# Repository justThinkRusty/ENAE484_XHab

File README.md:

# ENAE484_XHab
 This is a repository for Class of 2020 X-Hab Capstone Projecct revision and repository control. 
Unfortunately, due to the non-binary nature of NX files, collaboration between individuals in sub 
teams is going to be necessary to avoid merge conflicts (i.e. when two individuals work on the 
same assmebly file at the same time). If this occurs, one person's adjustments must be discarded
to be able to keep the repository moving. 

Additionally, please make comments with every commit to your branch so everyone can be up to date
with what changes were made. 

More subfolders can (and should) be made as we progress through the project, potentially such as
a Matlab folder or a Big Picture CAD program.

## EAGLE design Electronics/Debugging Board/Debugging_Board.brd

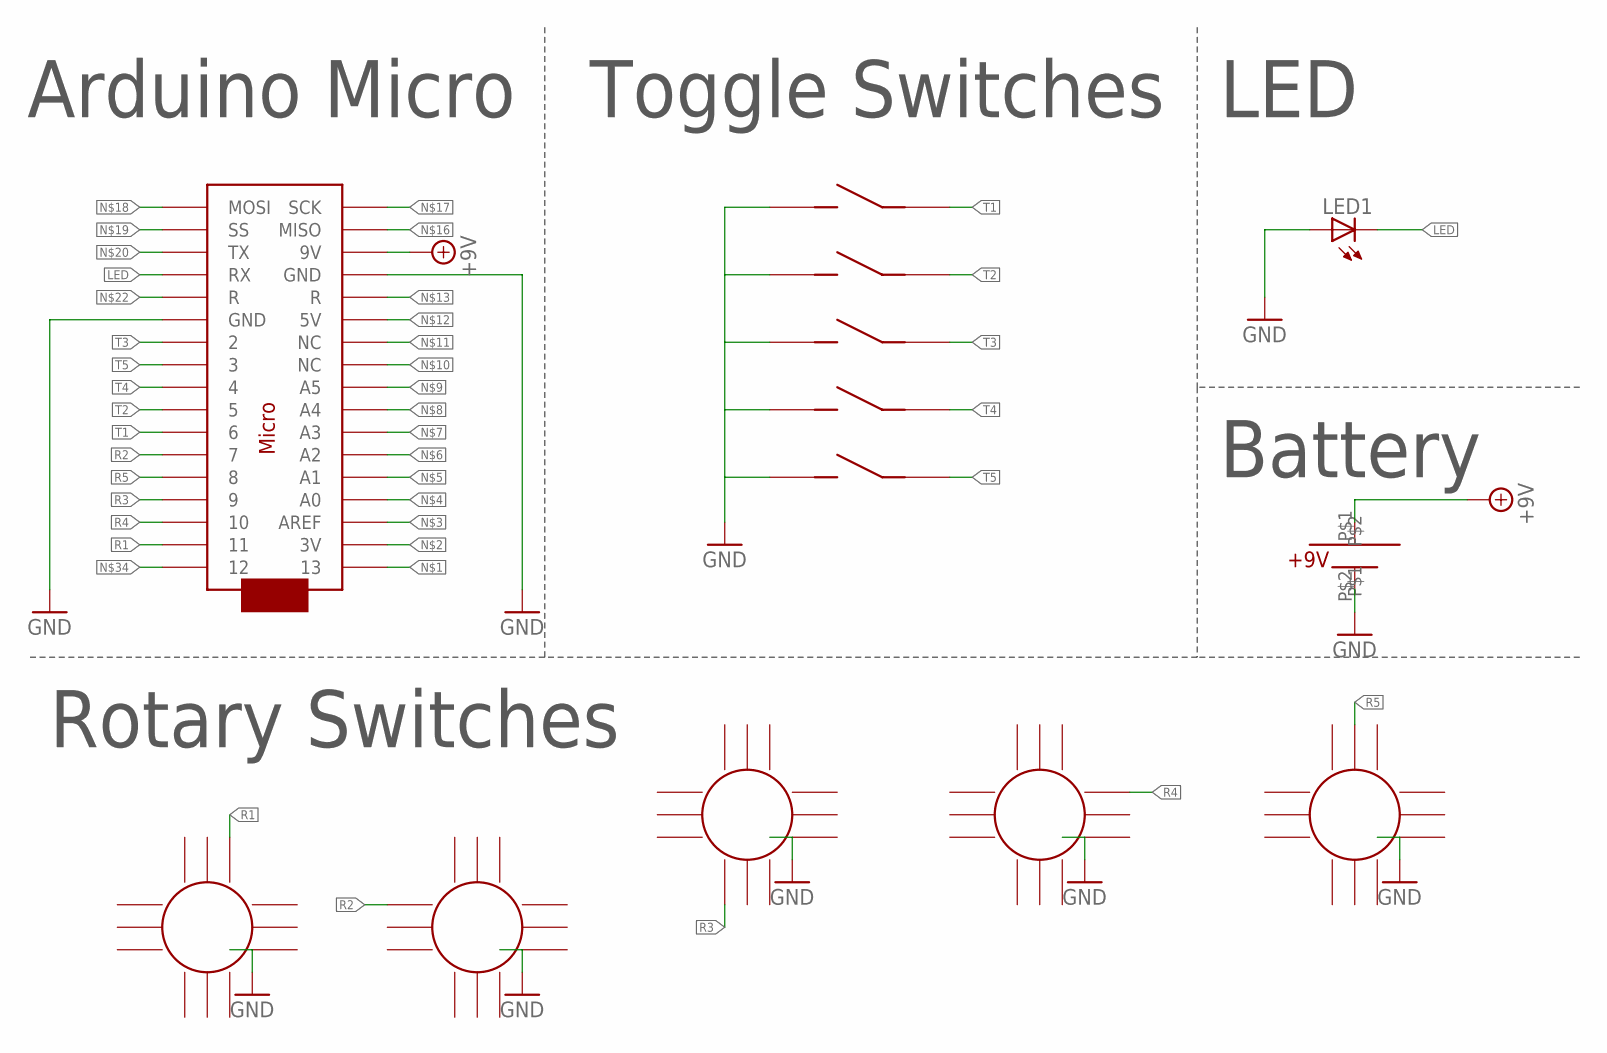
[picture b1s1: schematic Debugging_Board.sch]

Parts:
LED1: LED5MM
U$1: ARDUINOMICRO
U$2, U$3, U$4, U$5, U$6: TOGGLE; SWITCH
U$7, U$8, U$9, U$10, U$11: ROTARY
U$12: BATTERY

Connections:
+9V: U$1.P$20 (9V), U$12.P$1
GND: LED1.A, U$1.P$12 (GND), U$1.P$21 (GND), U$2.P$1, U$3.P$1, U$4.P$1, U$5.P$1, U$6.P$1, U$7.P$13, U$8.P$13, U$9.P$13, U$10.P$13, U$11.P$13, U$12.P$2
LED: LED1.K (C), U$1.P$14 (RX)
R1: U$1.P$2 (11), U$7.P$3
R2: U$1.P$6 (7), U$8.P$12
R3: U$1.P$4 (9), U$9.P$9
R4: U$1.P$3 (10), U$10.P$4
R5: U$1.P$5 (8), U$11.P$2
T1: U$1.P$7 (6), U$2.P$2
T2: U$1.P$8 (5), U$3.P$2
T3: U$1.P$11 (2), U$4.P$2
T4: U$1.P$9 (4), U$5.P$2
T5: U$1.P$10 (3), U$6.P$2

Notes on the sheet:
Arduino Micro
Toggle Switches
Rotary Switches
LED
Battery

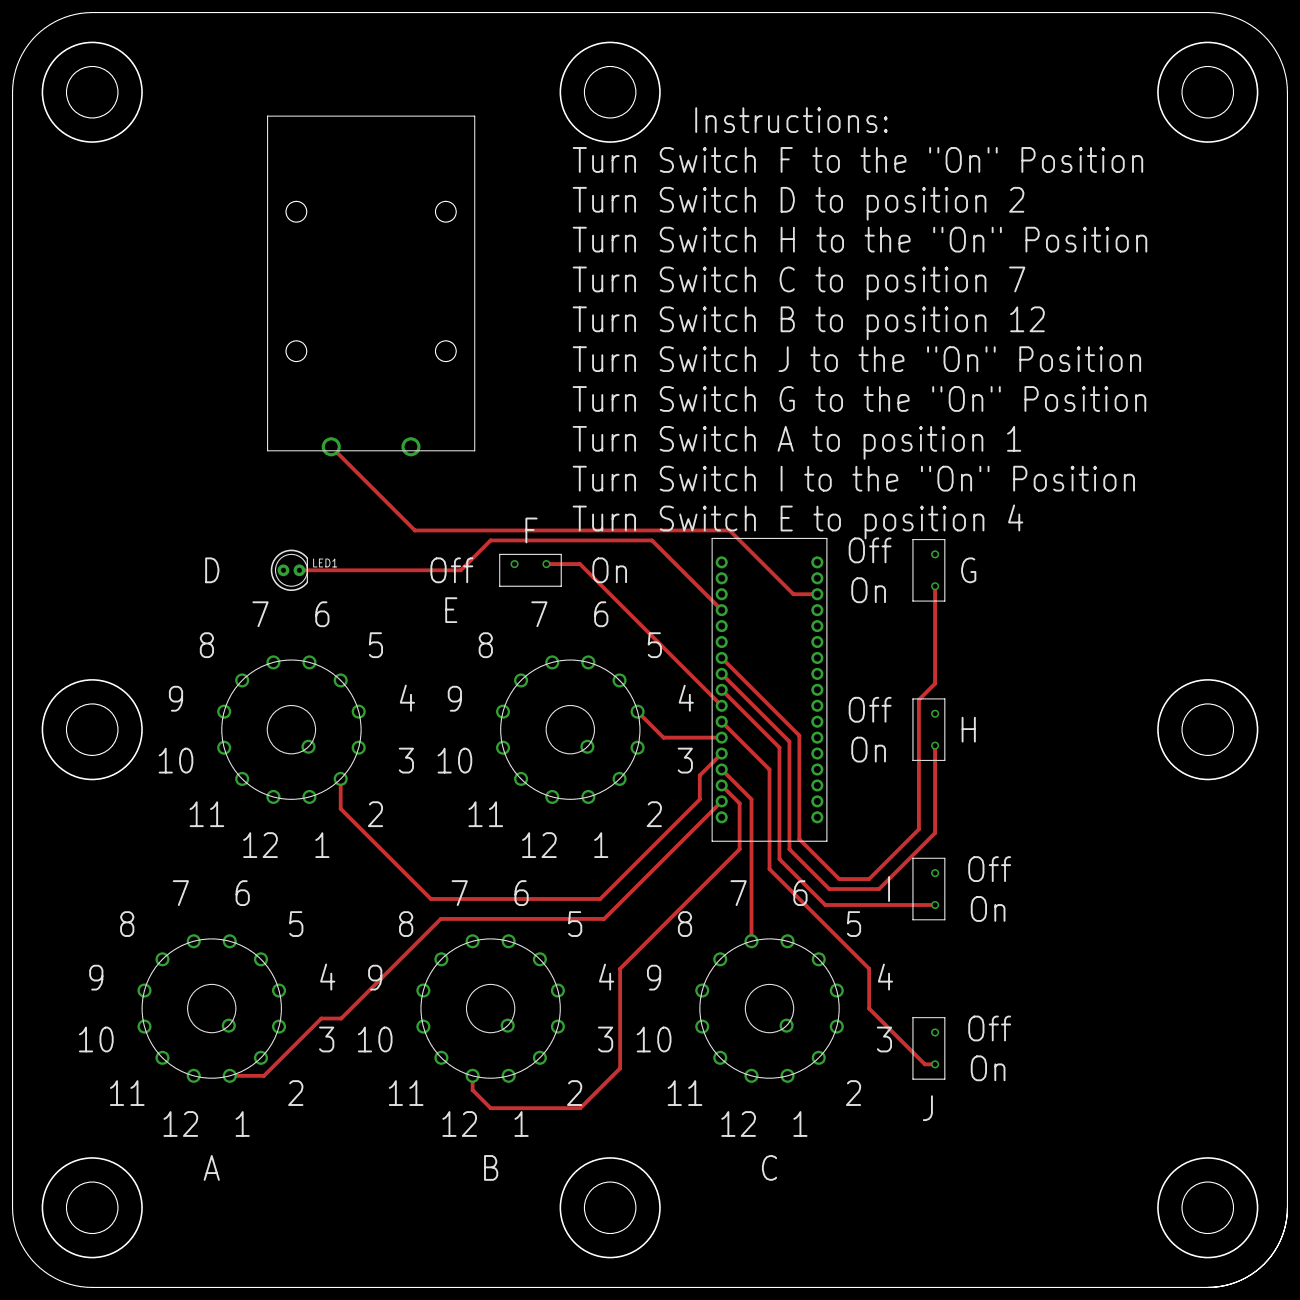
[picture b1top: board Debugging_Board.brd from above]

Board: 2 copper layers, 203.2 x 203.2 mm, 13 parts (0 on the bottom side), 13 nets.

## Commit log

2020-01-28 Added initial components from 8020, made repository viewable publically, and all assemblies creatd before class start
2020-01-28 Update of README.md to include more detail
2020-01-29 Added IRB folder and the TLX/Cooper Harper rating forms for test subject evaluation
2020-02-03 Create IRB notes
2020-02-10 Hinge Hardware
    Added hinge hardware and fixed constraint on baseUnit
2020-02-12 XHab Overall Design added and IRB docs
2020-02-15 More rack assembly
2020-02-15 Additional Mockups
    Variable circular rack assebmly. Crtl + E and change num_of_racks
2020-02-19 Updating parts
2020-02-19 Overhead Medical and Food Storage Module
    First iteration of the overhead medical and food storage module. Used to simulate removal and storage of medical equipment, as well as the dehydrated food pouches (applesauce)
2020-02-19 Assemblies update
2020-02-19 Adding hand controller parts
2020-02-19 Add files via upload
    V1
2020-02-20 Create parts
2020-02-20 Create Medical assembly
    created an assembly for the Medical table. containing Matt's storage, Chirayu's table, and other parts.
2020-02-20 Create blabla
2020-02-20 Add files via upload
    I put together an assembly for the medical rack. it includes Matt's and Chirayu's components.
2020-03-02 Parts for the medical table assembly
2020-03-02 files for
2020-03-03 OSM - PDR Level Completed
    Where the OSM is at as of 3/2/2020, including some screencaps used in slide deck
2020-05-04 Added 4BMS CAD and a CS Folder
2020-05-04 Updated CAD to fit both differing radii
2020-05-04 Addd indiviudal pieces for each habitat
2020-05-05 water processing systems CADS (without hoses for simplicity)
2020-05-06 Rearranged the table name to reflect final assembly as ASSY_F
2020-05-06 water - now in the right scale!
2020-05-06 CTB Rack
    Adjust the size of CTB_RACK using expressions
    CTB's currently have to be manually placed.
2020-05-08 Initial commit for the integrated assemblies
2020-05-08 Add files via upload
    water process reupload
2020-05-11 Create 40_surface_assembly.prt
    initial commit of 40_surface_assembly.prt
2020-05-11 assemblies for both 20, and all microgravity assemblies
2020-05-11 Update 40_surface_assembly.prt
    Mostly assembled
2020-05-11 Floors for real
2020-05-12 Updated 4BMS_20 to have rounded top and bottom to fit in the hab curves
2020-05-12 METOX oven CADED and ready for integration
2020-05-12 Created comm/battery/logistics rack assembly
2020-05-12 Dimension save error
2020-05-12 Update 40_surface_assembly.prt
    moved beds, put in geolab
2020-05-12 Integrated new berths into 40_surface_assembly.prt
2020-05-12 Add files via upload
    Updated Airlock CAD
2020-05-13 Updated 40_surface_assembly.prt with all currently ready parts.
2020-05-13 Revert "Merge branch 'master' of https://github.com/justThinkRusty/ENAE484_XHab"
    This reverts commit a59e2aaa2059aea098cef48c2ea7751f602e040f, reversing
    changes made to f984f06e5f248c9bd950200b92aac05338f4d73d.
2020-05-13 Commit of Hudson's heatexchanger v1
2020-05-13 added heat exchangers
2020-05-13 Rearranged, need rounded hygiene for 40_surface_assembly.prt
2020-05-13 Mostly finished small micro/surface habs
2020-05-13 40 microg hab assembly
2020-05-13 Added CTB's for all items, integrated into surface_40
2020-05-13 updated small microg
2020-05-13 40m microg
2020-05-13 Added storage to 20_surface_assembly
2020-05-13 added storage to 20_microg_assembly
2020-05-13 Water process reupload and 1 tank
2020-05-13 80m surface
2020-05-13 80m microg
2020-05-13 All Floors Added
    All floors added to microg and surface habitats
2020-05-14 lots of updates to various asssemblies
2020-05-14 now taking floor slats into account
2020-05-14 added storage to all habitats
2020-05-14 added updated bathrooms
2020-05-14 added CEVIS Cycle
2020-05-14 tank for the 20 m^3 micro habitat
2020-05-14 20 m^3 micro hab fix
2020-05-14 added treadmill and cycle to all habs
2020-05-14 All components present.
2020-05-14 small tweaks to 40_microg
2020-05-14 Hab Orthogrid Shell
2020-05-14 Updated assemblieswith radiators
2020-05-19 color coded CAD assemblies + staircase

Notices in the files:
parts and their libraries:
SparkFun: Licensing: CC v3.0 Share-Alike You are welcome to use this library for commercial purposes.
